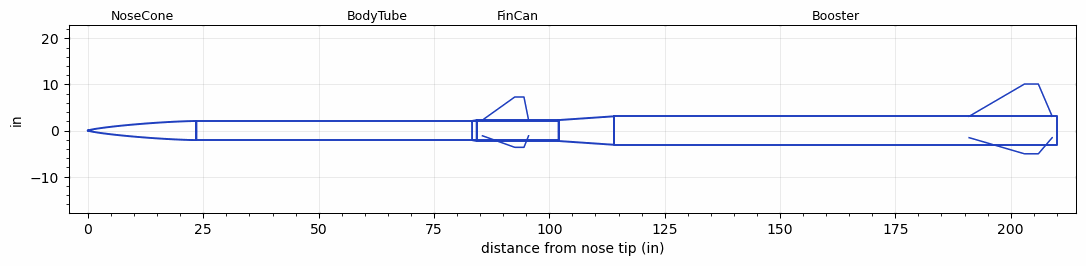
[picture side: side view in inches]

<RASAeroDocument>
 <FileVersion>2</FileVersion>
 <RocketDesign>
  <NoseCone>
   <Length>23.5</Length>
   <Diameter>4.14</Diameter>
   <Shape>Von Karman Ogive</Shape>
   <Location>0</Location>
  </NoseCone>
  <BodyTube>
   <Length>78.5</Length>
   <Diameter>4.14</Diameter>
   <Location>23.5</Location>
  </BodyTube>
  <FinCan>
   <Length>17.75</Length>
   <Diameter>4.54</Diameter>
   <InsideDiameter>4.14</InsideDiameter>
   <Location>102</Location>
   <ShoulderLength>1</ShoulderLength>
   <Offset>-17.75</Offset>
   <Fin>
    <Count>3</Count>
    <Chord>10</Chord>
    <Span>5</Span>
    <SweepDistance>7</SweepDistance>
    <TipChord>2</TipChord>
    <Thickness>0.125</Thickness>
    <Location>16.5</Location>
    <AirfoilSection>Hexagonal</AirfoilSection>
    <FX1>0.5</FX1>
    <FX3>0.5</FX3>
   </Fin>
  </FinCan>
  <Booster>
   <Length>96</Length>
   <Diameter>6.17</Diameter>
   <InsideDiameter>4.54</InsideDiameter>
   <Location>102</Location>
   <ShoulderLength>12</ShoulderLength>
   <Fin>
    <Count>3</Count>
    <Chord>18</Chord>
    <Span>7</Span>
    <SweepDistance>12</SweepDistance>
    <TipChord>3</TipChord>
    <Thickness>0.125</Thickness>
    <Location>19</Location>
    <AirfoilSection>Hexagonal</AirfoilSection>
    <FX1>1</FX1>
    <FX3>1</FX3>
   </Fin>
  </Booster>
  <Surface>Smooth Paint</Surface>
  <ModifiedBarrowman>True</ModifiedBarrowman>
  <Turbulence>True</Turbulence>
  <UseBooster1>False</UseBooster1>
  <UseBooster2>False</UseBooster2>
 </RocketDesign>
 <LaunchSite>
  <Altitude>4000</Altitude>
  <Pressure>0</Pressure>
  <RodAngle>0</RodAngle>
  <RodLength>4</RodLength>
  <Temperature>74</Temperature>
  <WindSpeed>0</WindSpeed>
 </LaunchSite>
 <Recovery>
  <Altitude1>1000</Altitude1>
  <Altitude2>1000</Altitude2>
  <DeviceType1>None</DeviceType1>
  <DeviceType2>None</DeviceType2>
  <Event1>False</Event1>
  <Event2>False</Event2>
  <Size1>1</Size1>
  <Size2>1</Size2>
  <EventType1>None</EventType1>
  <EventType2>None</EventType2>
  <CD1>1.33</CD1>
  <CD2>1.33</CD2>
 </Recovery>
 <SimulationList>
  <Simulation>
   <SustainerEngine>O3400-IM-P  (CTI)</SustainerEngine>
   <SustainerLaunchWt>58.8</SustainerLaunchWt>
   <SustainerNozzleDiameter>2.7</SustainerNozzleDiameter>
   <SustainerCG>58.8</SustainerCG>
   <SustainerIgnitionDelay>10</SustainerIgnitionDelay>
   <Booster1Engine>P8000  (CTI)</Booster1Engine>
   <Booster1LaunchWt>217.4</Booster1LaunchWt>
   <Booster1SeparationDelay>0.5</Booster1SeparationDelay>
   <Booster1IgnitionDelay>0</Booster1IgnitionDelay>
   <Booster1CG>133.6</Booster1CG>
   <Booster1NozzleDiameter>6</Booster1NozzleDiameter>
   <IncludeBooster1>True</IncludeBooster1>
   <Booster2Delay>0</Booster2Delay>
   <IncludeBooster2>False</IncludeBooster2>
   <TimetoApogee>138.4574</TimetoApogee>
   <MaxAltitude>250436.7</MaxAltitude>
   <MaxVelocity>4119.513</MaxVelocity>
  </Simulation>
 </SimulationList>
</RASAeroDocument>
